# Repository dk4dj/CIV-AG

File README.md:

# WT32-ETH01 — CI-V → Antenna Genius Bridge

Arduino sketch for the **WT32-ETH01** (ESP32 + LAN8720). Reads Icom CI-V frequency and TX status, automatically switches a **4O3A Antenna Genius** antenna selector, and provides reliable TX inhibit for both the Icom transceiver and SmartSDR/FlexRadio via a two-layer interlock implementation. An optional **EA DOGL128W-6** display with rotary encoder provides on-device status, antenna selection, and system information.

---

## Features

- **Automatic AG discovery** — UDP broadcast on port 9007; extracts IP, port, serial, firmware, ports, antennas, mode, uptime
- **Full AG configuration readout** — band table and antenna list on every connect
- **CI-V frequency tracking** on UART2 — transceiver address learned automatically; active polling (Cmd 0x03) after `CIV_BROADCAST_TIMEOUT_MS` (1 s)
- **CI-V TX status** (Cmd 0x1C/0x00) polled every 200 ms — drives TX/RX indicator on display and web UI
- **Automatic band → antenna mapping** based on AG TX masks
- **Four-layer TX protection** — all controlled together via `setConflict()`:
  - GPIO4 HIGH → hardware PTT inhibit line
  - CI-V Cmd 0x16/0x66 → TX Inhibit on newer Icom transceivers
  - FlexRadio server `state=PTT_REQUESTED` → AG sets `inhibit=1` on Port B
  - SmartSDR Ethernet Interlock `not_ready` → SmartSDR TX blocked directly
- **Conflict reason display** — web UI and log show which transceiver was inhibited with address, frequency and antenna name
- **Correct conflict detection** — `wantedAntId` tracks the last requested antenna independently of AG status (AG sets `txant=0` when `inhibit=1`); re-evaluated on every Port B update
- **Source=AUTO guard** — ignores AG startup state for own port until first CI-V frame received
- **CI-V timeout** (`CIV_TIMEOUT_MS` = 5 s) — releases port and activates all inhibit mechanisms
- **FlexRadio two-layer implementation:**
  - **Server** (port 4992, up to `FLEX_MAX_CLIENTS` = 4): emulates a FlexRadio for the AG; sends `PTT_REQUESTED` proactively after `keepalive enable`
  - **Client**: connects to real FLEX radio; `interlock create type=ANT model=... valid_antennas=`; `not_ready`/`ready` with hex interlock ID
- **Separate UDP sockets** — `flexDiscUdp` (send-only) and `flexListenUdp` (receive-only on port 4992) to avoid ESP32 conflict
- **Automatic FLEX radio selection** — priority: AG Port 2 nickname → NVS default IP → single radio → user selection
- **Persistent default radio** — NVS (`Preferences`), survives reboot
- **Shared JSON builder** `buildStatusJson()` — identical data for SSE push and `/api` polling
- **Band-ID lookup** by `bands[i].id` (AG Band-IDs are 1-based; array is 0-based)
- **Splash screen** at boot (128×64 px, PROGMEM)
- **Display inversion** on any conflict or CI-V timeout (ST7565 hardware invert)
- **Built-in web interface** on port 80 with live SSE, FLEX selection panel, conflict detail
- **Log export** — `GET /log`, 300 timestamped entries
- **Non-blocking architecture** throughout
- **DHCP** — no network configuration required

---

## Hardware

### GPIO Assignment

| Signal | GPIO | Notes |
|---|---|---|
| ETH CLK input | 0 | `ETH_CLOCK_GPIO0_IN`, from LAN8720 crystal |
| ETH Power/Reset | 16 | LAN8720 nRST — try `-1` if boot shows reset timeout |
| ETH MDC | 23 | |
| ETH MDIO | 18 | |
| ETH RMII (fixed) | 19, 21, 22, 25, 26, 27 | Cannot be reassigned |
| CI-V RX (UART2) | 5 | 1 kΩ pull-up to 3.3 V recommended |
| CI-V TX (UART2) | 17 | Active polling + TX Inhibit frames |
| TX inhibit / conflict output | 4 | HIGH = any conflict or CI-V timeout active |
| Display SI (MOSI) | 15 | Software-SPI |
| Display SCK | 14 | Software-SPI |
| Display CS | 12 | Active low |
| Display A0 | 2 | Strapping pin — safe after boot |
| Display RST | 33 | Active low |
| Encoder A | 39 | Input-only, ISR CHANGE, ext. 10 kΩ pull-up **required** |
| Encoder B | 36 | Input-only, ISR CHANGE, ext. 10 kΩ pull-up **required** |
| Encoder button | 35 | Input-only, polled, ext. 10 kΩ pull-up **required** |

> GPIO 35/36/39 are input-only with no internal pull-ups. GPIO 36/39 lie in register `GPIO.in1.val` (not `GPIO.in`). The ISR reads both pins as `(GPIO.in1.val >> (PIN - 32)) & 1`.

---

## Display & Encoder

### Menu states

| State | How to enter | How to leave |
|---|---|---|
| `MENU_STATUS` | Default / timeout | Short press → `MENU_ANT_SELECT`; long press ≥1s → `MENU_INFO` |
| `MENU_INFO` | Long press ≥1s from Status | Any press → `MENU_STATUS` |
| `MENU_ANT_SELECT` | Short press from Status or rotate | Press → `MENU_CONFIRM`; timeout |
| `MENU_CONFIRM` | Press from Ant Select | Press (confirm) or timeout |
| `MENU_FLEX_SELECT` | Automatic when multiple FLEX radios found | Short press = select; long press ≥2s = select + set NVS default |

### Status screen layout
```
21.465 MHz              RX     ← TX/RX indicator (inverted block when TX)
Band: 15m
Ant:  Beam_OB11-3
AG: OK  Port A           ← bottom status bar
```

### Info screen (long press)
```
WT32: 192.168.1.202
AG:   192.168.1.221
FW:4.1.8 S/N:C7-F6-42
FLEX: 192.168.1.100
      (Flexi)
────────────────────
CI-V: 0x94   19200 Bd
[Taste]=zurück
```

### Encoder: full 4-state Gray-code decoding
Both channels (GPIO 39/36) trigger `CHANGE` interrupts. The ISR uses a 4-bit state machine — only valid Gray-code transitions count; glitches and crosstalk are filtered automatically. Adjust `ENC_PULSES_PER_DETENT` (default 4) if steps are missed or doubled.

---

## Web Interface

Open `http://<device-ip>/` in any browser.

| Section | Content |
|---|---|
| Funkgerät (CI-V) | Address, frequency, active band, TX/RX status |
| Antenna Genius | Name, IP, firmware, uptime, status |
| Port-Belegung | Port A/B antenna/band, **Funkgerät TX** (from Cmd 0x1C), conflict badge with inhibited TRX details, FlexRadio status |
| FLEX-Radio-Auswahl | Yellow warning card when multiple radios found |
| Band-/Antennen-Konfiguration | Full AG tables |
| Debug-Log | Live SSE log, 300 entries, download |

**Endpoints:** `GET /`, `GET /api`, `GET /events`, `GET /log`, `POST /flex-select?ip=`, `POST /flex-default?ip=`

---

## CI-V Protocol Details

| Command | Direction | Purpose |
|---|---|---|
| `FE FE <trx> E0 03 FD` | WT32 → TRX | Poll frequency |
| `FE FE <trx> E0 00 FD` | TRX → WT32 | Frequency broadcast |
| `FE FE E0 <trx> 00 ... FD` | TRX → WT32 | Frequency response |
| `FE FE <trx> E0 1C 00 FD` | WT32 → TRX | Poll TX status (every 200 ms) |
| `FE FE E0 <trx> 1C 00 00 FD` | TRX → WT32 | RX status |
| `FE FE E0 <trx> 1C 00 01 FD` | TRX → WT32 | TX status |
| `FE FE <trx> E0 16 66 01 FD` | WT32 → TRX | TX Inhibit ON |
| `FE FE <trx> E0 16 66 00 FD` | WT32 → TRX | TX Inhibit OFF |

---

## FlexRadio Interlock

### Server (AG interlock)
- VITA-49 discovery broadcast every 2 s + TCP server port 4992
- Sends `S00000000|interlock state=PTT_REQUESTED` immediately after `keepalive enable`
- Log prefix: `[FLEX:N]`

### Client (SmartSDR direct interlock)
```
→ C1|client program CIV-Bridge
→ C2|interlock create type=ANT model=CIV-Bridge serial=DK4DJ-1 valid_antennas=
← R2|0|000000F4          ← hex interlock ID
→ C3|interlock not_ready 000000F4   ← conflict
→ C4|interlock ready 000000F4       ← resolved
```
- Log prefix: `[FRINT]`
- FLEX radio IP from `ip=` field in VITA-49 payload (more reliable than UDP sender IP)
- Auto-select priority: AG Port 2 nickname → NVS default → single radio → user

---

## TX Inhibit Mechanisms

All controlled via `setConflict(bool active, const char *reason)`:

| Layer | Mechanism | Effect |
|---|---|---|
| GPIO4 HIGH | `digitalWrite` | Hardware PTT line to TRX |
| CI-V 0x16/0x66 | Serial2 frame | Icom TX Inhibit (newer models) |
| FlexRadio server | `PTT_REQUESTED` status | AG `inhibit=1` on Port B |
| FlexRadio client | `interlock not_ready` | SmartSDR TX blocked directly |

`conflictReason` is built with CI-V address, frequency and antenna name. Set before `wantedAntId = 0` so the last active antenna appears in the conflict message.

---

## Antenna Conflict Detection

### wantedAntId

The AG sets `txant=0` in status messages when `inhibit=1`. Without a separate tracking variable `portTxAnt[AG_RADIO_PORT-1]` would become 0, causing false "no conflict" decisions.

`wantedAntId` is set in `setAGPort()`, cleared in `releaseAGPort()`, and never overwritten by AG status updates. `checkAndSignalConflict()` uses it as fallback when called with argument 0.

### Antenna menu filtering (`menuBuildAntList`)

The selection menu excludes:
- `activeAnt` — already active on own port
- `blockedAnt = portTxAnt[otherIdx]` — currently used by SmartSDR

This prevents selecting an antenna that is already occupied on either port.

---

## Setup

### Arduino IDE

| Setting | Value |
|---|---|
| Board | ESP32 Dev Module |
| Flash Mode | QIO |
| Flash Size | 4 MB |
| ESP32 core | Espressif ESP32 Arduino ≥ 2.x |

### Libraries

| Library | When required |
|---|---|
| ETH, WiFiUdp, WiFiClient, WiFiServer, WebServer, Preferences | Always (ESP32 core) |
| U8g2 by olikraus | `DISPLAY_ENABLED 1` |

### Key Configuration Constants

```cpp
#define DISPLAY_ENABLED          1
#define FLEX_EMULATION_ENABLED   1
#define AG_RADIO_PORT            1      // 1=Port A, 2=Port B
#define ETH_POWER_PIN            16     // try -1 on some board revisions
#define CONFLICT_PIN             4
#define CIV_BAUD                 19200
#define CIV_BROADCAST_TIMEOUT_MS 1000   // active poll after 1 s without broadcast
#define CIV_TIMEOUT_MS           5000   // release port after 5 s without CI-V
#define FLEX_INTERLOCK_NAME      "CIV-Bridge"
#define FLEX_INTERLOCK_SERIAL    "DK4DJ-1"
#define FLEX_MAX_CLIENTS         4
#define FLEX_MAX_RADIOS          8
#define ENC_PULSES_PER_DETENT    4      // 4 for most encoders; try 2 or 1 if steps skip
#define DISP_CONTRAST            45
#define DEBUG_CONFLICT           0      // set to 1 for conflict diagnostic logging
#define LOG_BUF_LINES            300
```

---

## Troubleshooting

| Symptom | Likely cause | Fix |
|---|---|---|
| `TG1WDT_SYS_RESET` at boot | Wrong `ETH_POWER_PIN` | Try `ETH_POWER_PIN -1` |
| AG not found | UDP blocked | Check `[DISC]` in log |
| SmartSDR still transmits | FLEX radio not connected | Check `[FRINT]` entries in log |
| No `[FRINT]` entries | `flexListenUdp` not receiving | Verify port 4992 not blocked |
| Interlock ID −1 | `interlock create` rejected | Check `[FRINT] <<` responses |
| Conflict after band change | AG `txant=0` during inhibit | Handled by `wantedAntId` |
| Port A/B shows `---` | Port released after timeout | Normal — clears on next CI-V |
| Encoder skips steps | Wrong `ENC_PULSES_PER_DETENT` | Try values 1, 2, 4 |
| TX indicator wrong | TRX does not respond to Cmd 0x1C | Check CI-V Transceive setting |
| Conflict at startup | AG reports old session state | Handled by source=AUTO guard |

---

## License

GNU General Public License v3.0

*Developed with the assistance of [Claude.ai](https://claude.ai) by Anthropic.*

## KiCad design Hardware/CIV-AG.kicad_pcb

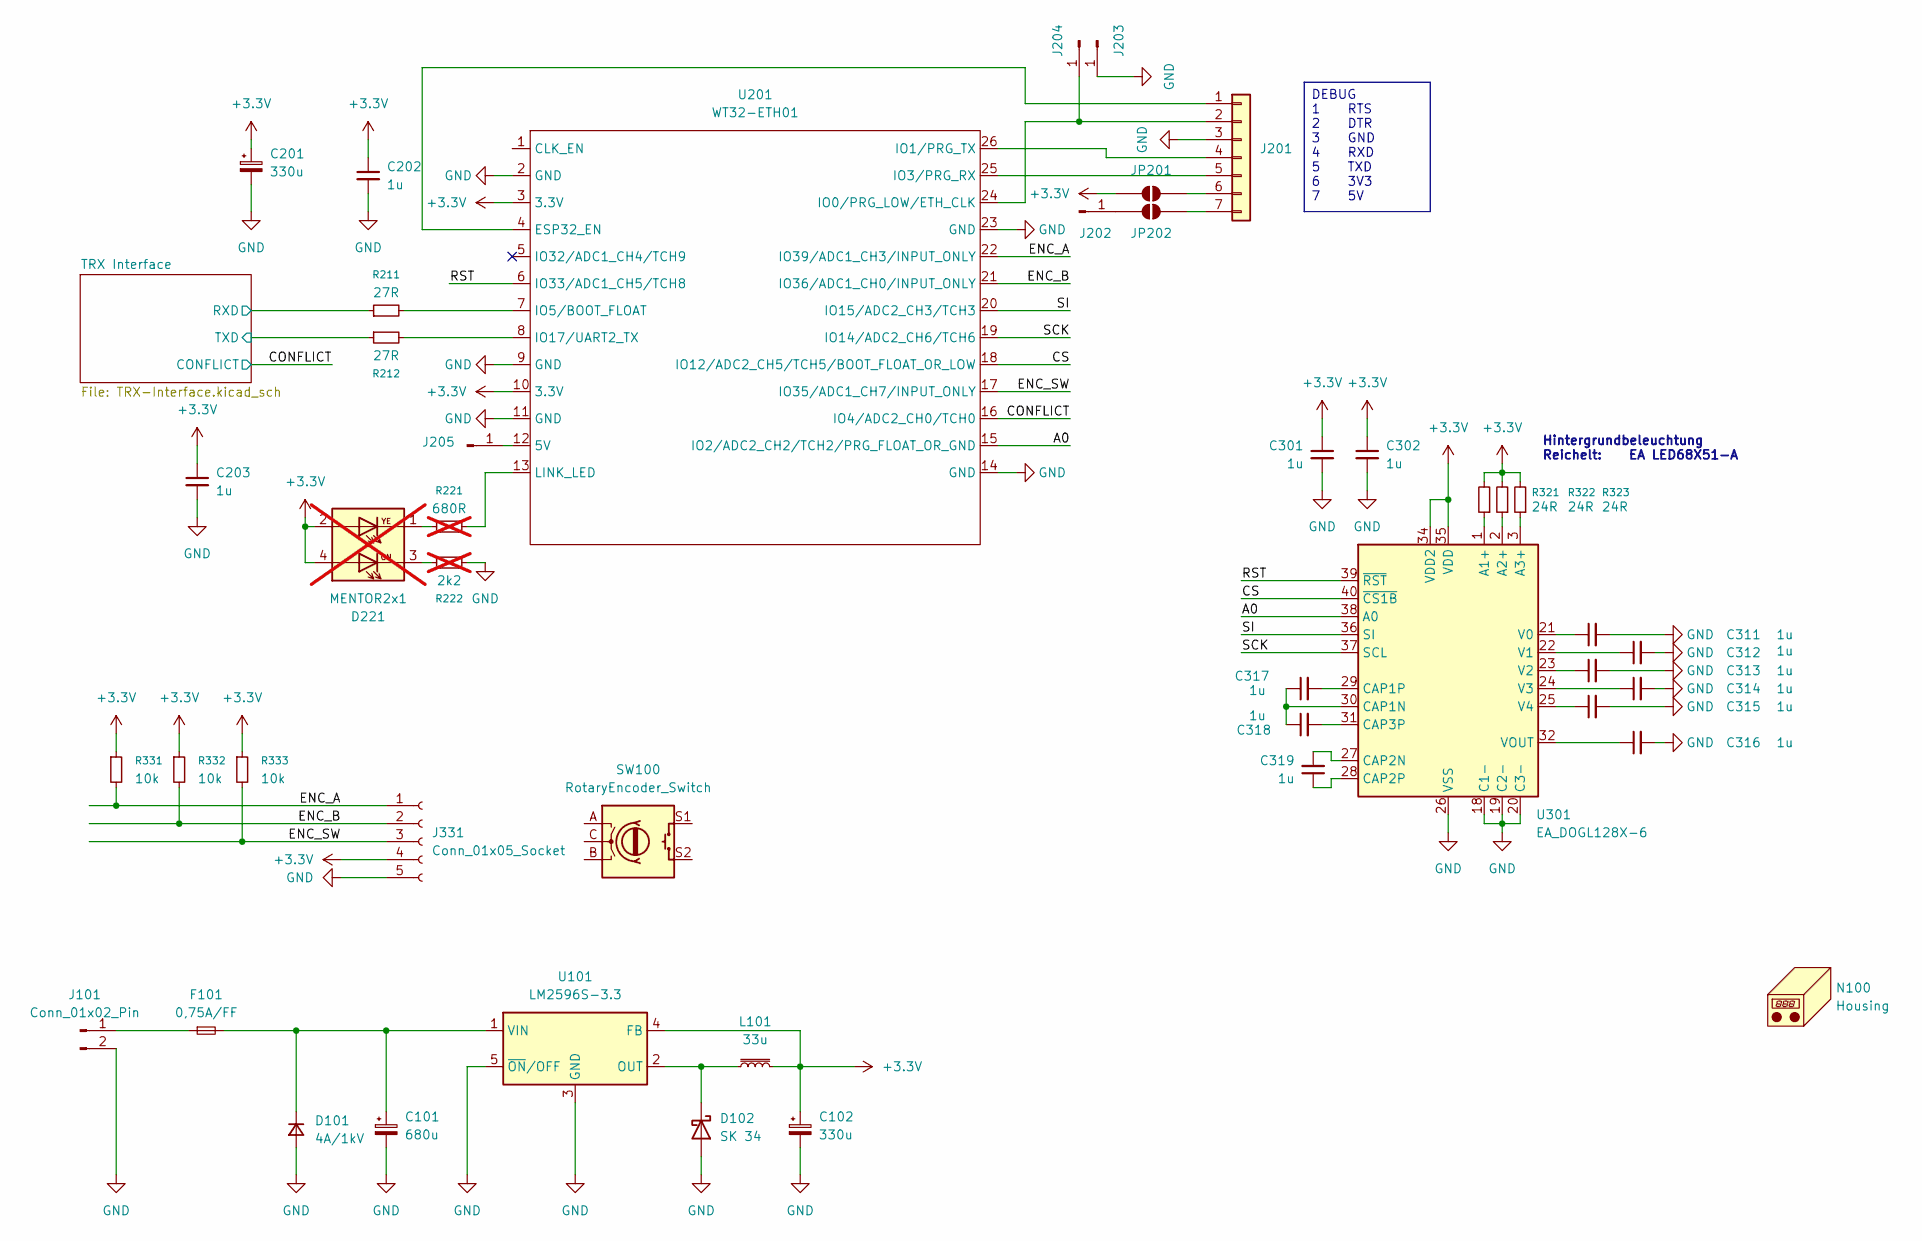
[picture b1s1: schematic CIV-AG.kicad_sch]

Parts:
C101: 680u; CP_Elec_10x10.5
C102, C201: 330u; CP_Elec_6.3x7.7
C202, C203, C301, C302, C311, C312, C313, C314, C315, C316, C317, C318, C319: 1u; C_0805_2012Metric_Pad1.18x1.45mm_HandSolder
D101: 4A/1kV; D_SMC_Handsoldering
D102: SK 34; D_SMA_Handsoldering
D221: MENTOR2x1; not fitted
F101: 0,75A/FF; Fuseholder_Littelfuse_Nano2_154x; DigiKey F1221CT-ND
J101: Conn_01x02_Pin; JST_EH_B2B-EH-A_1x02_P2.50mm_Vertical
J201: BL 15 SMD 043 7; PinSocket_1x07_P2.54mm_Vertical_SMD_Pin1Left; DigiKey 5496-BL15SMD0437-ND
J202, J203, J204, J205: Conn_01x01_Pin; SolderWirePad_1x01_SMD_2x4mm
J331: Conn_01x05_Socket; PinSocket_1x05_P2.54mm_Vertical
JP201, JP202: SolderJumper_2_Open; SolderJumper-2_P1.3mm_Open_RoundedPad1.0x1.5mm
L101: 33u; L_Fastron_PISR_Handsoldering
N100: Housing; DigiKey HM1719-ND
R211, R212: 27R; R_0805_2012Metric_Pad1.20x1.40mm_HandSolder
R221: 680R; R_0805_2012Metric_Pad1.20x1.40mm_HandSolder; not fitted
R222: 2k2; R_0805_2012Metric_Pad1.20x1.40mm_HandSolder; not fitted
R321, R322, R323: 24R; R_0805_2012Metric_Pad1.20x1.40mm_HandSolder
R331, R332, R333: 10k; R_0805_2012Metric_Pad1.20x1.40mm_HandSolder
SW100: RotaryEncoder_Switch
U101: LM2596S-3.3; TO-263-5_TabPin3; DigiKey LM2596S-3.3/NOPB-ND
U201: WT32-ETH01; WT32-ETH01_SMD; DigiKey 1597-102991455-ND
U301: EA_DOGL128X-6; EA_DOGL128-6; DigiKey 1481-1058-ND

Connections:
+3.3V: C102.1, C201.1, C202.1, C203.1, C301.1, C302.1, D221.2 (KB), D221.4 (KR), J331.4, JP201.1 (A), L101.2, R321.2, R322.2, R323.2, R331.1, R332.1, R333.1, U101.4 (FB), U201.3 (3.3V), U201.10 (3.3V), U301.34 (VDD2), U301.35 (VDD); also elsewhere on the board
/A0: U201.15 (IO2/ADC2_CH2/TCH2/PRG_FLOAT_OR_GND), U301.38 (A0)
/CONFLICT: U201.16 (IO4/ADC2_CH0/TCH0); also elsewhere on the board
/CS: U201.18 (IO12/ADC2_CH5/TCH5/BOOT_FLOAT_OR_LOW), U301.40 (~CS1B)
/ENC_A: J331.1, R331.2, U201.22 (IO39/ADC1_CH3/INPUT_ONLY)
/ENC_B: J331.2, R332.2, U201.21 (IO36/ADC1_CH0/INPUT_ONLY)
/ENC_SW: J331.3, R333.2, U201.17 (IO35/ADC1_CH7/INPUT_ONLY)
/RST: U201.6 (IO33/ADC1_CH5/TCH8), U301.39 (~RST)
/SCK: U201.19 (IO14/ADC2_CH6/TCH6), U301.37 (SCL)
/SI: U201.20 (IO15/ADC2_CH3/TCH3), U301.36 (SI)
/TRX Interface/RXD: R211.1; also elsewhere on the board
/TRX Interface/TXD: R212.1; also elsewhere on the board
GND: C101.2, C102.2, C201.2, C202.2, C203.2, C301.2, C302.2, C311.2, C312.2, C313.2, C314.2, C315.2, C316.2, D101.2 (A), D102.2 (A), J101.2, J201.3, J203.1 (Pin_1_1), J331.5, R222.2, U101.3 (GND), U101.5 (~ON/OFF), U201.2 (GND), U201.9 (GND), U201.11 (GND), U201.14 (GND), U201.23 (GND), U301.18 (C1-), U301.19 (C2-), U301.20 (C3-), U301.26 (VSS), U301.33 (VSS); also elsewhere on the board
unnamed: C101.1, D101.1 (K), F101.2, U101.1 (VIN)
unnamed: D102.1 (K), L101.1, U101.2 (OUT)
unnamed: D221.1 (AB), R221.1
unnamed: D221.3 (AR), R222.1
unnamed: F101.1, J101.1
unnamed: J201.1, U201.4 (ESP32_EN)
unnamed: J201.2, J204.1 (Pin_1_1), U201.24 (IO0/PRG_LOW/ETH_CLK)
unnamed: J201.4, U201.26 (IO1/PRG_TX)
unnamed: J201.5, U201.25 (IO3/PRG_RX)
unnamed: J201.6, JP201.2 (B)
unnamed: J201.7, JP202.2 (B)
unnamed: J202.1 (Pin_1_1), JP202.1 (A)
unnamed: J205.1 (Pin_1_1), U201.12 (5V)
unnamed: R211.2, U201.7 (IO5/BOOT_FLOAT)
unnamed: R212.2, U201.8 (IO17/UART2_TX)
unnamed: R221.2, U201.13 (LINK_LED)
unnamed: R321.1, U301.1 (A1+)
unnamed: R322.1, U301.2 (A2+)
unnamed: R323.1, U301.3 (A3+)
unnamed: C317.1, C318.1, U301.30 (CAP1N)
unnamed: C317.2, U301.29 (CAP1P)
unnamed: C319.2, U301.27 (CAP2N)
unnamed: C319.1, U301.28 (CAP2P)
unnamed: C318.2, U301.31 (CAP3P)
unnamed: C311.1, U301.21 (V0)
unnamed: C312.1, U301.22 (V1)
unnamed: C313.1, U301.23 (V2)
unnamed: C314.1, U301.24 (V3)
unnamed: C315.1, U301.25 (V4)
unnamed: C316.1, U301.32 (VOUT)

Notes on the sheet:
Hintergrundbeleuchtung Reichelt: EA LED68X51-A
DEBUG 1 RTS 2 DTR 3 GND 4 RXD 5 TXD 6 3V3 7 5V

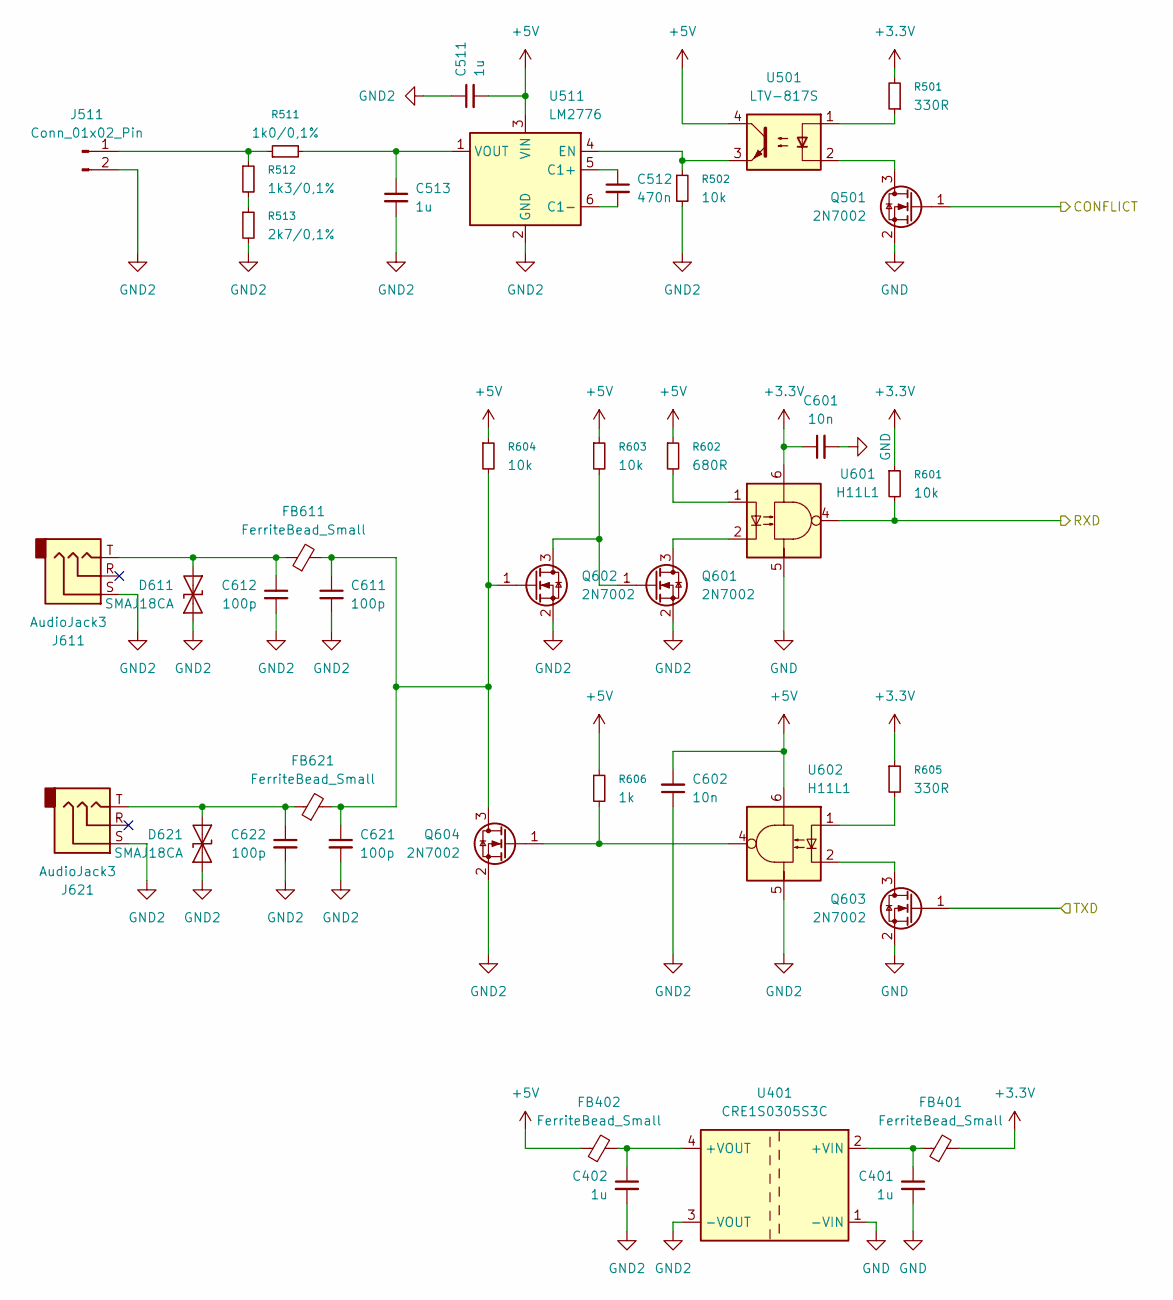
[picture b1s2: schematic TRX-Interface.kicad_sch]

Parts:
C401, C402, C511, C513: 1u; C_0805_2012Metric_Pad1.18x1.45mm_HandSolder
C512: 470n; C_0805_2012Metric_Pad1.18x1.45mm_HandSolder
C601, C602: 10n; C_0805_2012Metric_Pad1.18x1.45mm_HandSolder
C611, C612, C621, C622: 100p; C_0805_2012Metric_Pad1.18x1.45mm_HandSolder
D611, D621: SMAJ18CA; D_SMA
FB401, FB402, FB611, FB621: FerriteBead_Small; L_0805_2012Metric_Pad1.05x1.20mm_HandSolder; DigiKey 732-1606-1-ND
J511: Conn_01x02_Pin; JST_EH_B2B-EH-A_1x02_P2.50mm_Vertical
J611, J621: AudioJack3; Jack_3.5mm_Lumberg_1503_07_Horizontal
Q501, Q601, Q602, Q603, Q604: 2N7002; SOT-23
R501, R605: 330R; R_0805_2012Metric_Pad1.20x1.40mm_HandSolder
R502, R601, R603, R604: 10k; R_0805_2012Metric_Pad1.20x1.40mm_HandSolder
R511: 1k0/0,1%; R_0805_2012Metric_Pad1.20x1.40mm_HandSolder
R512: 1k3/0,1%; R_0805_2012Metric_Pad1.20x1.40mm_HandSolder
R513: 2k7/0,1%; R_0805_2012Metric_Pad1.20x1.40mm_HandSolder
R602: 680R; R_0805_2012Metric_Pad1.20x1.40mm_HandSolder
R606: 1k; R_0805_2012Metric_Pad1.20x1.40mm_HandSolder
U401: CRE1S0305S3C; Converter_DCDC_Murata_CRE1xxxxxx3C_THT; DigiKey 811-3193-ND
U501: LTV-817S; SMDIP-4_W9.53mm
U511: LM2776; SOT-23-6; DigiKey 296-43957-1-ND
U601, U602: H11L1; DIP-6_W8.89mm_SMDSocket_LongPads; DigiKey H11L1SR2MCT-ND

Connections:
+3.3V: C601.1, FB401.2, R501.2, R601.1, R605.1, U601.6; also elsewhere on the board
+5V: C511.2, C602.2, FB402.1, R602.1, R603.1, R604.1, R606.1, U501.4, U511.3 (VIN), U602.6
/CONFLICT: Q501.1 (G); also elsewhere on the board
/TRX Interface/RXD: R601.2, U601.4; also elsewhere on the board
/TRX Interface/TXD: Q603.1 (G); also elsewhere on the board
GND: C401.2, C601.2, Q501.2 (S), Q603.2 (S), U401.1 (-VIN), U601.5; also elsewhere on the board
GND2: C402.2, C511.1, C513.2, C602.1, C611.2, C612.2, C621.2, C622.2, D611.1 (A1), D621.1 (A1), J511.2, J611.S, J621.S, Q601.2 (S), Q602.2 (S), Q604.2 (S), R502.2, R513.2, U401.3 (-VOUT), U511.2 (GND), U602.5
unnamed: C612.1, D611.2 (A2), FB611.1, J611.T
unnamed: C622.1, D621.2 (A2), FB621.1, J621.T
unnamed: J511.1, R511.1, R512.1
unnamed: Q501.3 (D), U501.2
unnamed: Q601.3 (D), U601.2
unnamed: Q601.1 (G), Q602.3 (D), R603.2
unnamed: C611.1, C621.1, FB611.2, FB621.2, Q602.1 (G), Q604.3 (D), R604.2
unnamed: Q603.3 (D), U602.2
unnamed: Q604.1 (G), R606.2, U602.4
unnamed: R501.1, U501.1
unnamed: R512.2, R513.1
unnamed: R602.2, U601.1
unnamed: R605.2, U602.1
unnamed: C401.1, FB401.1, U401.2 (+VIN)
unnamed: C402.1, FB402.2, U401.4 (+VOUT)
unnamed: C512.1, U511.5 (C1+)
unnamed: C512.2, U511.6 (C1-)
unnamed: R502.1, U501.3, U511.4 (EN)
unnamed: C513.1, R511.2, U511.1 (VOUT)

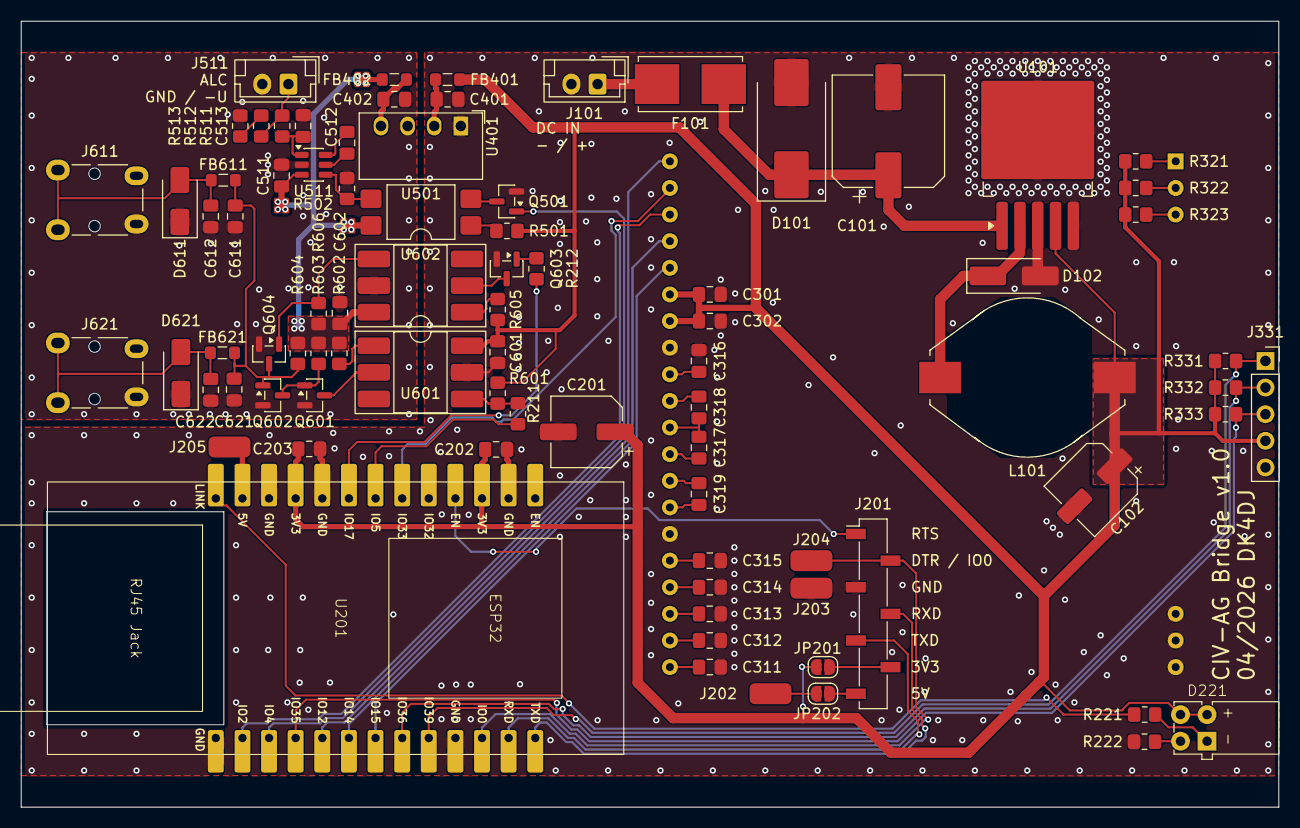
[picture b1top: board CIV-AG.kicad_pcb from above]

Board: 2 copper layers, 120.0 x 75.0 mm, 84 parts (1 on the bottom side), 64 nets.

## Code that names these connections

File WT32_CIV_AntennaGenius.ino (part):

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#define AG_RADIO_PORT   1       // Radio-Port A = 1

// ─── Konflikt-Ausgang ────────────────────────────────────────────────────────
#define CONFLICT_PIN    4
#define DEBUG_CONFLICT  0   // 1 = checkAndSignalConflict logt jeden Check (Debugging)

// ─── Display (EA DOGL128W-6, ST7565, Software-SPI) ──────────────────────────
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#define DISP_RST_PIN    33   // RST des DOGL128 (active low)

// ─── Drehencoder ─────────────────────────────────────────────────────────────
#define ENC_A_PIN       39   // Encoder Kanal A  (input-only, ext. Pull-up, ISR)
#define ENC_B_PIN       36   // Encoder Kanal B  (input-only, ext. Pull-up)
#define ENC_BTN_PIN     35   // Encoder Taster   (input-only, ext. Pull-up)
// Hinweis: GPIO35/36/39 sind input-only ohne internen Pull-up.
// Externe Pull-up-Widerstände (10 kΩ) an 3.3 V sind zwingend erforderlich!
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  static uint8_t state = 0;
  // GPIO 32-39 liegen im Register GPIO.in1.val (nicht GPIO.in das nur GPIO 0-31 abdeckt).
  // Direktzugriff: Bit = (PIN - 32) in GPIO.in1.val
  uint8_t a = (GPIO.in1.val >> (ENC_A_PIN - 32)) & 1;
  uint8_t b = (GPIO.in1.val >> (ENC_B_PIN - 32)) & 1;
  state = ((state << 2) | (a << 1) | b) & 0x0F;
  // Nur die vier gueltigen Gray-Code-Vorwaerts- und Rueckwaertsuebergaenge zaehlen
  // Vorwaerts:  00→01  01→11  11→10  10→00  (state: 1,7,14,8)
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  memset(bands,    0, sizeof(bands));
  memset(antennas, 0, sizeof(antennas));

  pinMode(CONFLICT_PIN, OUTPUT);
  digitalWrite(CONFLICT_PIN, LOW);
  webLog("[CONF] Konflikt-Ausgang: GPIO%d", CONFLICT_PIN);

#if DISPLAY_ENABLED
  displaySetup();
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void setConflict(bool active, const char *reason) {
  if (conflictActive == active) return;
  conflictActive = active;
  digitalWrite(CONFLICT_PIN, active ? HIGH : LOW);
  if (active) {
    // Gesperrten Transceiver bestimmen: CI-V (Port A) wird immer durch uns gesperrt
    // da der FLEX-Radio über seinen eigenen Interlock informiert wird.
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      snprintf(conflictReason, sizeof(conflictReason),
               "CI-V-TRX gesperrt &ndash; Ant %s", antName);
    webLog("[CONF] Sperre aktiv:     GPIO%d=HIGH (%s) → %s",
           CONFLICT_PIN, reason, conflictReason);
  } else {
    conflictReason[0] = '\0';
    webLog("[CONF] Sperre aufgehoben: GPIO%d=LOW  (%s)", CONFLICT_PIN, reason);
  }
  sendCIVTxInhibit(active);
#if FLEX_EMULATION_ENABLED
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</head>
<body>
<h1>&#128225; WT32-ETH01 &mdash; CI-V &rarr; Antenna Genius Bridge</h1>
<div id="conflict-banner">&#9888; ANTENNEN-KONFLIKT &mdash; <span id="conflict-detail">Ziel-Antenne bereits von anderem Port belegt</span> &mdash; GPIO4 = HIGH</div>
<div class="grid">
  <div class="card">
    <h2>Funkger&auml;t (CI-V)</h2>
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  document.getElementById('txA').innerHTML=d.txA?`<span class="badge badge-tx">&#128308; SENDEN</span>`:`<span class="badge badge-muted">RX</span>`;
  document.getElementById('txB').innerHTML=d.txB?`<span class="badge badge-tx">&#128308; SENDEN</span>`:`<span class="badge badge-muted">RX</span>`;
  const cb=document.getElementById('conflictBadge');
  const banner=document.getElementById('conflict-banner');
  const detail=document.getElementById('conflict-detail');
  if(d.conflict){
    const r=d.conflictReason||'Ziel-Antenne bereits von anderem Port belegt';
    cb.innerHTML=`<span class="badge badge-red">&#9888; KONFLIKT &ndash; ${r}</span>`;
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void displaySetup() {
  // Encoder-Pins
  // GPIO35/36/39: input-only, kein interner Pull-up → ext. 10 kΩ an 3.3 V nötig
  pinMode(ENC_A_PIN,   INPUT);   // ext. Pull-up erforderlich
  pinMode(ENC_B_PIN,   INPUT);   // ext. Pull-up erforderlich
  pinMode(ENC_BTN_PIN, INPUT);   // ext. Pull-up erforderlich

  // ISR auf beide Flanken beider Kanaele A (GPIO39) und B (GPIO36).
  // Die 4-Bit-State-Machine in encISR() filtert Glitches durch Crosstalk automatisch.
  attachInterrupt(digitalPinToInterrupt(ENC_A_PIN), encISR, CHANGE);
  attachInterrupt(digitalPinToInterrupt(ENC_B_PIN), encISR, CHANGE);

  // Display initialisieren
  u8g2.begin();
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
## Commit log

2026-04-06 Create test
2026-04-12 First FLEX emulation integration
